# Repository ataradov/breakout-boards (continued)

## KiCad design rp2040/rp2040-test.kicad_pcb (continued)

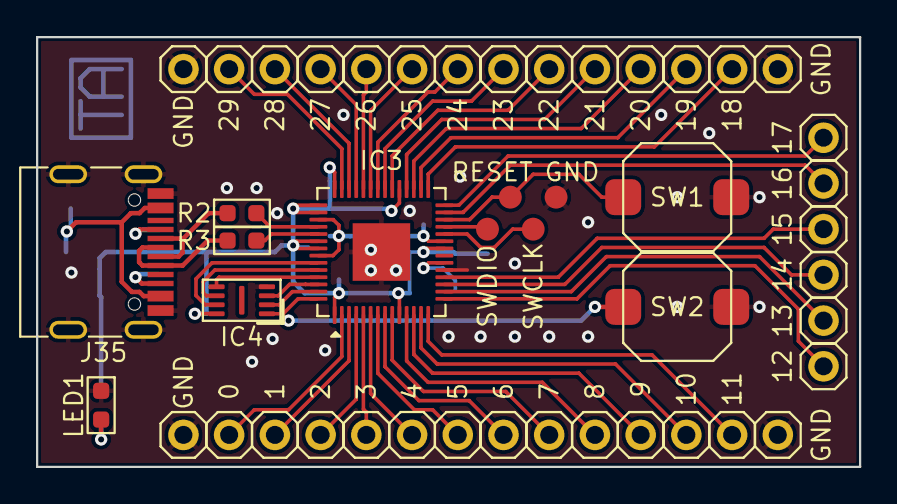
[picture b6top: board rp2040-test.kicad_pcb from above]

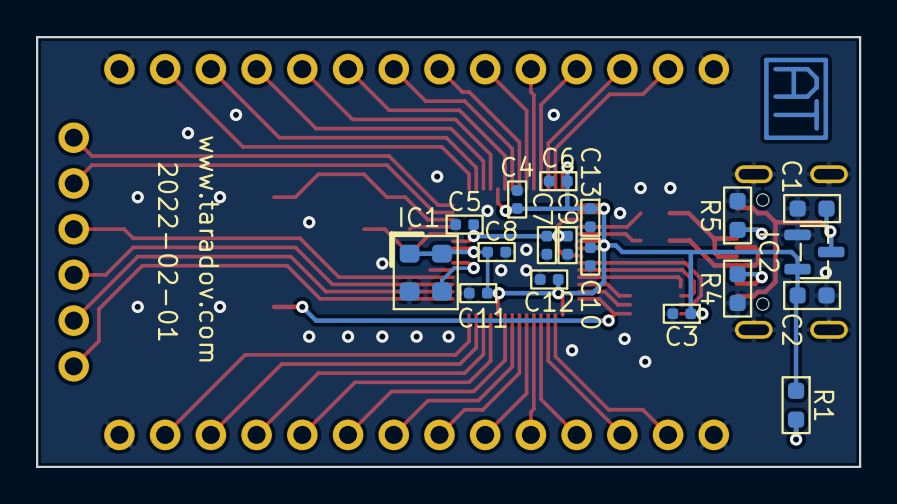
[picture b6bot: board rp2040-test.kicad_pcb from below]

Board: 2 copper layers, 45.7 x 23.9 mm, 65 parts (19 on the bottom side), 51 nets.

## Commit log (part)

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2019-04-28 Added initial boards
2019-04-28 Added pictures
2019-04-30 Added SAME70 pictures
2019-10-07 Added a board for GD32F407V
2019-12-29 Added boards for Lattice LCMXO256C and LCMXO2-2000HC
2019-12-30 Typos
2020-01-15 Added demo projects for lcmxo2-2000hc and lcmxo256c
2020-01-15 Added pictures for lcmxo2-2000hc and lcmxo256c
2020-12-02 Added Nuvoton M484SIDAE
2021-01-16 Added a small USB test board with a USB A plug
2022-02-18 Added RP2040 board
2022-02-18 Modified readme for the RP2040 board
2022-02-18 Added pictures for RP2040
2025-08-30 Added T20Q100F3 and STM32H7
2025-10-26 Added STM32G441KB board
